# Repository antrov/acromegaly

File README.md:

Acromegaly is an open source project of the desk with automatically adjustable height. Position of the desk is controlled by Bluetooth Low Energy interface and dedicated iOS Application. 

Provided designs allows
* to build a mechanical frame of the desk, 
* to manufacture and program a controller and finally 
* to build a BLE client app. 

Total cost of components, manufacture and final polish is around 100$. 

## CAD project

[GitHub repo](https://github.com/antrov/acromegaly/tree/master/CAD)
 
Full documentation of mechanical parts of the desk: frame, rails, driver mounting and desktop. Supplied in english and polish.

Designed and created by Msc Leszek Andrzejewski.

## PCB schematic and design

[GitHub repo](https://github.com/antrov/acromegaly/tree/master/PCB)

[Eagle](https://www.autodesk.com/products/eagle/overview) files used to design and manufacture the base PCB with a BLE controller and driver connectors. Besides, board includes an op-amp used to amplify current measurements for ADC, as well as a 8MB Flash memory. 

## BLE controller (nRF51)

[GitHub repo](https://github.com/antrov/acromegaly-nrf51)

ANSI C code developed for the nRF51 MCU and based on its SDK. The brain of a desk controller, exposes interface for receiving commands from Bluetooth Low Energy and to broadcasts informations like: 
* current height, 
* target height, 
* movement state and direction, 
* current power 

Configured to compile with wide available and free toolchains.

## BLE client (iOS)

[GitHub repo](https://github.com/antrov/acromegaly-ios)

Swift iOS application used to present visually state of the desk and control it remotely.

* auto scanning and connecting to dedicated Acromegaly BLE device
* visual representation of current and requested desk height
* setting exact height of a desk
* swipe gesture to set bounding positions
* storing of the favourites positions

## Contact
In case of new issues, concepts or just a will to say hello:

* antrof@gmail.com
* https://www.linkedin.com/in/handr/

## License 

Copyright 2019 Hubert Andrzejewski

This code is distributed under the terms and conditions of the MIT license.

```
Permission is hereby granted, free of charge, to any person obtaining a copy of
this software and associated documentation files (the "Software"), to deal in
the Software without restriction, including without limitation the rights to
use, copy, modify, merge, publish, distribute, sublicense, and/or sell copies of
the Software, and to permit persons to whom the Software is furnished to do so,
subject to the following conditions:

The above copyright notice and this permission notice shall be included in all
copies or substantial portions of the Software.

THE SOFTWARE IS PROVIDED "AS IS", WITHOUT WARRANTY OF ANY KIND, EXPRESS OR
IMPLIED, INCLUDING BUT NOT LIMITED TO THE WARRANTIES OF MERCHANTABILITY, FITNESS
FOR A PARTICULAR PURPOSE AND NONINFRINGEMENT. IN NO EVENT SHALL THE AUTHORS OR
COPYRIGHT HOLDERS BE LIABLE FOR ANY CLAIM, DAMAGES OR OTHER LIABILITY, WHETHER
IN AN ACTION OF CONTRACT, TORT OR OTHERWISE, ARISING FROM, OUT OF OR IN
CONNECTION WITH THE SOFTWARE OR THE USE OR OTHER DEALINGS IN THE SOFTWARE.
```

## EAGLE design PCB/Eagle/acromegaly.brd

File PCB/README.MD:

# Acromegaly PCB

[Eagle](https://www.autodesk.com/products/eagle/overview) files used to design and manufacture the base PCB with a BLE controller and driver connectors. Besides, board includes an op-amp used to amplify current measurements for ADC, as well as a 8MB Flash memory. 

## Required parts:
* 2mm raster 4x9 connectors
* 2.74mm raster goldpin connectors
* M45PE80 - 8MB FLASH Memory
* LM358 - op-amp for current measurement
* double BTS 7960 as H-Bridge driver - [sample](http://www.alselectro.com/motor-driver-hbridge-43amps-bts7960.html)
* LM3671 3.3V Buck Converter Breakout - 3.3V - step-down power supply from 5V to 3.3V - [sample](https://www.adafruit.com/product/2745)
* nRF51 Core Board - 2mm raster pins - [sample](https://www.waveshare.com/core51822.htm)
* 4x 1MΩ -  SMD 1206 Resitors
* LM393 with slot detector - [sample](https://www.electrokit.com/produkt/modul-med-optisk-lasgaffel/)
* Mask for slot detector - [PDF](https://github.com/antrov/acromegaly/tree/master/PCB/gap_mask.pdf)

## Flashing

During development on DK board, flashing is done by integrated JLink (SEGGER) programmer. In order to flash Acromegaly PCB it is necessary to connect DK VVC/GND instead of LM3671 and SWDIO/SWCLK to dedicated PCB connectors accoriding to [following rules](https://electronut.in/nrf51-dk-external-programming/)

## Slot detector

[Mask PDF](https://github.com/antrov/acromegaly/tree/master/PCB/gap_mask.pdf)

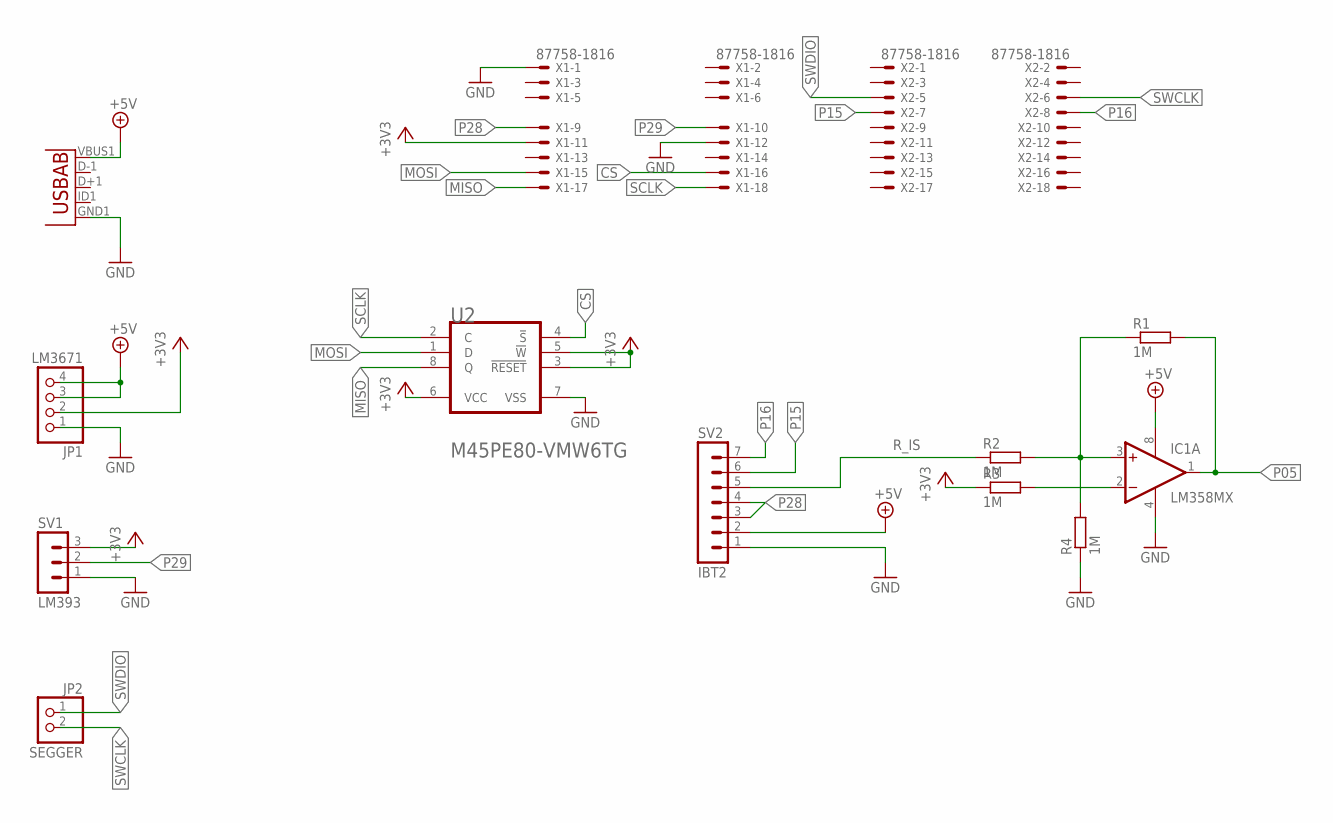
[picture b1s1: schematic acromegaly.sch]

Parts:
IC1: LM358MX; SO08
JP1: LM3671; 1X04
JP2: SEGGER; 1X02
R1, R2, R3, R4: 1M; M1206
SV1: LM393; MA03-1
SV2: IBT2; MA07-1
U1: USB""; USB-MICRO-SMD
U2: MICRON_M45PE80-VMW6TGMICRON_M45PE80-VMW6TG_0_0; MICRON_M45PE80-VMW6TG_0
X1, X2: 87758-1816

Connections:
+3V3: JP1.2, R3.1, SV1.3, U2.3 (!RESET!), U2.5 (!W!), U2.6 (VCC), X1.11
+5V: IC1.8 (V+), JP1.3, JP1.4, SV2.2, U1.VBUS1 (VBUS)
CS: U2.4 (!S!), X1.16
GND: IC1.4 (V-), JP1.1, R4.1, SV1.1, SV2.1, U1.GND1 (GND), U2.7 (VSS), X1.1, X1.12
MISO: U2.8 (Q), X1.17
MOSI: U2.1 (D), X1.15
unnamed: IC1.3 (+IN), R1.1, R2.2, R4.2
unnamed: IC1.2 (-IN), R3.2
P05: IC1.1 (OUT), R1.2
P15: SV2.6, X2.7
P16: SV2.7, X2.8
P28: SV2.3, SV2.4, X1.9
P29: SV1.2, X1.10
R_IS: R2.1, SV2.5
SCLK: U2.2 (C), X1.18
SWCLK: JP2.2, X2.6
SWDIO: JP2.1, X2.5

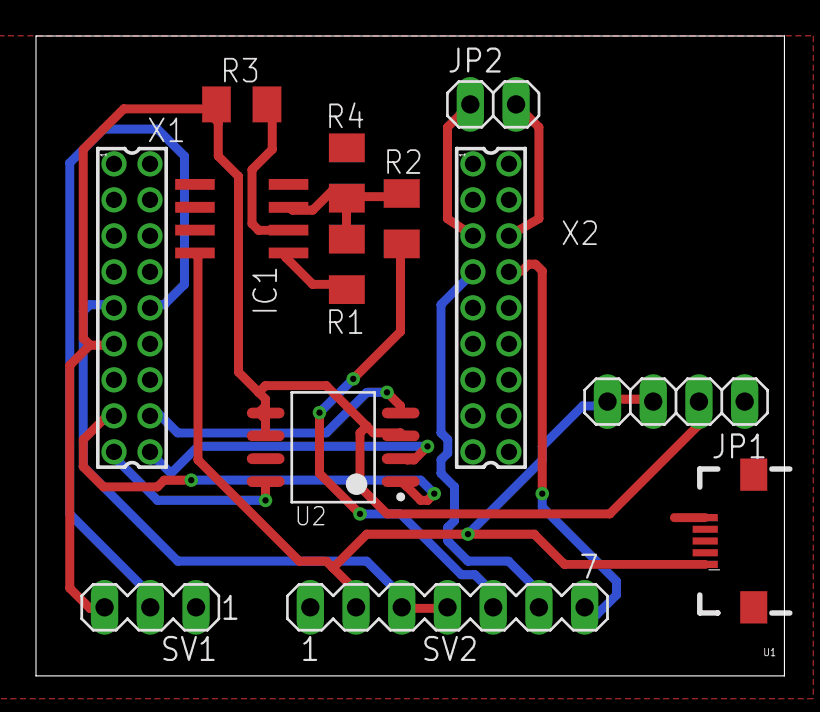
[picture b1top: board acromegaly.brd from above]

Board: 2 copper layers, 41.6 x 35.5 mm, 13 parts (0 on the bottom side), 17 nets.

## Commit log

2019-03-13 PCB and schematic for docs
2019-03-13 PCB resizsed
2019-03-13 CAD preview for docs
2019-03-13 README modified
2019-03-13 Rescaled
2019-03-13 Eagle files
2019-03-13 CAD designs as PDF files
2019-03-14 README updated
2019-03-14 PCB docs
2019-03-14 PCB photos
2019-03-14 PCB photo updated
2019-03-14 Slot sensors GIF
2019-03-22 Header image
2019-10-05 Demo GIF added
2019-10-05 Demo GIF updated#
